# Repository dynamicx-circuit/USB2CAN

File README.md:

# USB2CAN
## 现在的问题
需要把USB2CAN移植成Kicad库版本

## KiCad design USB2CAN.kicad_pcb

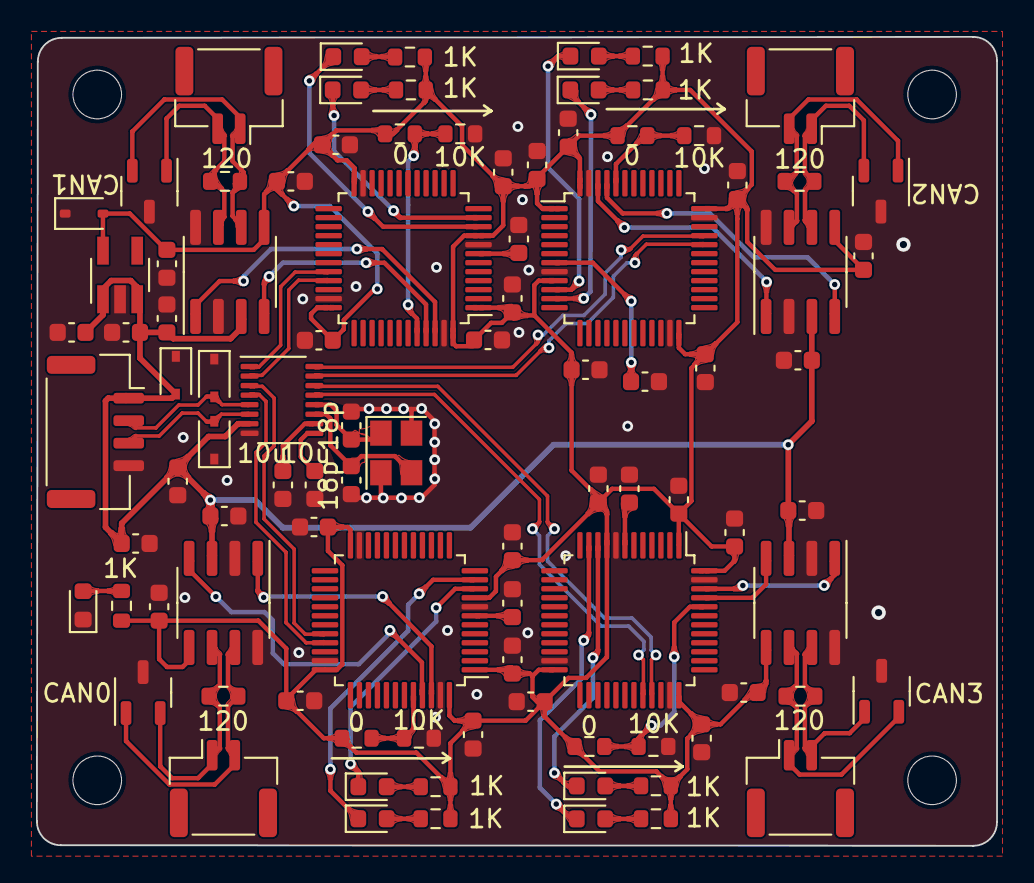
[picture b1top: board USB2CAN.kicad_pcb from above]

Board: 2 copper layers, 53.3 x 44.9 mm, 99 parts (0 on the bottom side), 58 nets.

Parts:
C1, C2, C3, C4, C5, C6, C7, C8, C9, C10, C11, C12, C13, C14, C15, C16, C17, C18, C19, C20, C21, C22, C23, C24, C25, C26, C27, C28, C29, C30, C31, C32, C33, C34, C35, C36, C41: 100n; C_0603_1608Metric
C37, C38: 10u; C_0603_1608Metric
C39, C40: 18p; C_0603_1608Metric
D1, D5, D6, D7, D8, D9, D10, D11, D12: LED; LED_0603_1608Metric
D2, D3, D4: BV05C; D_SOD-323
D13: BV03C; D_SOD-323
H1, H2, H3, H4: MountingHole; MountingHole_2.7mm_M2.5
J1: Conn_01x04; Molex_CLIK-Mate_502386-0470_1x04-1MP_P1.25mm_Horizontal
J2, J3, J4, J5: Conn_01x02; JST_GH_SM02B-GHS-TB_1x02-1MP_P1.25mm_Horizontal
R1, R4, R5, R9, R10, R14, R15, R19, R20: 1K; R_0603_1608Metric
R2, R7, R12, R17: 0; R_0603_1608Metric
R3, R8, R13, R18: 10K; R_0603_1608Metric
R6, R11, R16, R21: 120; R_0603_1608Metric
U1: HX9193; SOT-23-5_HandSoldering
U2, U4, U6, U8: STM32F072C8Tx; LQFP-48_7x7mm_P0.5mm
U3, U5, U7, U9: TJA1051T-3; SOIC-8_3.9x4.9mm_P1.27mm
U10: SL2.1S; SL2.1S-SSOP-16
U11, U12, U13, U14: SOT-23-3
Y1: 12M; Crystal_SMD_3225-4Pin_3.2x2.5mm

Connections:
+5V: C1.1, C2.1, C3.1, C12.1, C20.1, C28.1, C36.1, C41.1, D2.2 (A2), J1.1, U1.1 (VIN), U1.3 (EN), U3.3 (VCC), U5.3 (VCC), U7.3 (VCC), U9.3 (VCC), U10.7 (VDD5)
/STM1_CAN/CAN_H: J2.2, R11.1, U5.7 (CANH), U11.1 (H)
/STM1_CAN/CAN_L: J2.1, R11.2, U5.6 (CANL), U11.2 (L)
/STM1_CAN/CAN_RX: U4.45 (PB8), U5.4 (RXD)
/STM1_CAN/CAN_TX: U4.46 (PB9), U5.1 (TXD)
/STM1_CAN/LED1: D7.1 (K), U4.10 (PA0)
/STM1_CAN/LED2: D8.1 (K), U4.11 (PA1)
/STM1_CAN/USB_D+: U4.33 (PA12), U10.4 (DP1)
/STM1_CAN/USB_D-: U4.32 (PA11), U10.3 (DM1)
/STM2_CAN/CAN_H: J3.2, R6.1, U3.7 (CANH), U12.1 (H)
/STM2_CAN/CAN_L: J3.1, R6.2, U3.6 (CANL), U12.2 (L)
/STM2_CAN/CAN_RX: U2.45 (PB8), U3.4 (RXD)
/STM2_CAN/CAN_TX: U2.46 (PB9), U3.1 (TXD)
/STM2_CAN/LED1: D5.1 (K), U2.10 (PA0)
/STM2_CAN/LED2: D6.1 (K), U2.11 (PA1)
/STM2_CAN/USB_D+: U2.33 (PA12), U10.2 (DP2)
/STM2_CAN/USB_D-: U2.32 (PA11), U10.1 (DM2)
/STM_CAN3/CAN_H: J4.2, R21.1, U9.7 (CANH), U13.1 (H)
/STM_CAN3/CAN_L: J4.1, R21.2, U9.6 (CANL), U13.2 (L)
/STM_CAN3/CAN_RX: U8.45 (PB8), U9.4 (RXD)
/STM_CAN3/CAN_TX: U8.46 (PB9), U9.1 (TXD)
/STM_CAN3/LED1: D11.1 (K), U8.10 (PA0)
/STM_CAN3/LED2: D12.1 (K), U8.11 (PA1)
/STM_CAN3/USB_D+: U8.33 (PA12), U10.16 (DP3)
/STM_CAN3/USB_D-: U8.32 (PA11), U10.15 (DM3)
/STM_CAN4/CAN_H: J5.2, R16.1, U7.7 (CANH), U14.1 (H)
/STM_CAN4/CAN_L: J5.1, R16.2, U7.6 (CANL), U14.2 (L)
/STM_CAN4/CAN_RX: U6.45 (PB8), U7.4 (RXD)
/STM_CAN4/CAN_TX: U6.46 (PB9), U7.1 (TXD)
/STM_CAN4/LED1: D9.1 (K), U6.10 (PA0)
/STM_CAN4/LED2: D10.1 (K), U6.11 (PA1)
/STM_CAN4/USB_D+: U6.33 (PA12), U10.14 (DP4)
/STM_CAN4/USB_D-: U6.32 (PA11), U10.13 (DM4)
/USB_HUB/D+: D4.2 (A2), J1.3, U10.6 (UDP)
/USB_HUB/D-: D3.2 (A2), J1.2, U10.5 (UDM)
/USB_HUB/XIN: C40.1, U10.12 (XIN), Y1.1
/USB_HUB/XOUT: C39.1, U10.11 (XOUT), Y1.3
GND: C1.2, C2.2, C3.2, C4.2, C5.1, C6.2, C7.2, C8.2, C9.2, C10.2, C11.2, C12.2, C13.1, C14.2, C15.2, C16.2, C17.2, C18.2, C19.2, C20.2, C21.1, C22.2, C23.2, C24.2, C25.2, C26.2, C27.2, C28.2, C29.1, C30.2, C31.2, C32.2, C33.2, C34.2, C35.2, C36.2, C37.2, C38.2, C39.2, C40.2, C41.2, D1.1 (K), D2.1 (A1), D3.1 (A1), D4.1 (A1), D13.1 (A1), J1.4, R3.1, R8.1, R13.1, R18.1, U1.2 (GND), U2.8 (VSSA), U2.23 (VSS), U2.35 (VSS), U2.47 (VSS), U3.2 (GND), U3.8 (S), U4.8 (VSSA), U4.23 (VSS), U4.35 (VSS), U4.47 (VSS), U5.2 (GND), U5.8 (S), U6.8 (VSSA), U6.23 (VSS), U6.35 (VSS), U6.47 (VSS), U7.2 (GND), U7.8 (S), U8.8 (VSSA), U8.23 (VSS), U8.35 (VSS), U8.47 (VSS), U9.2 (GND), U9.8 (S), U10.8 (VSS), U11.3 (GND), U12.3 (GND), U13.3 (GND), U14.3 (GND), Y1.2, Y1.4
unnamed: D1.2 (A), R1.2
unnamed: D5.2 (A), R4.1
unnamed: D6.2 (A), R5.1
unnamed: D7.2 (A), R9.1
unnamed: D8.2 (A), R10.1
unnamed: D9.2 (A), R14.1
unnamed: D10.2 (A), R15.1
unnamed: D11.2 (A), R19.1
unnamed: D12.2 (A), R20.1
unnamed: R2.1, R3.2, U2.44 (BOOT0)
unnamed: C5.2, U2.7 (NRST)
unnamed: R7.1, R8.2, U4.44 (BOOT0)
unnamed: C13.2, U4.7 (NRST)
unnamed: R12.1, R13.2, U6.44 (BOOT0)
unnamed: C21.2, U6.7 (NRST)
unnamed: R17.1, R18.2, U8.44 (BOOT0)
unnamed: C29.2, U8.7 (NRST)
unnamed: C38.1, U10.10 (VDD18)
unnamed: C37.1, U10.9 (VDD33)
VCC: C4.1, C6.1, C7.1, C8.1, C9.1, C10.1, C11.1, C14.1, C15.1, C16.1, C17.1, C18.1, C19.1, C22.1, C23.1, C24.1, C25.1, C26.1, C27.1, C30.1, C31.1, C32.1, C33.1, C34.1, C35.1, D13.2 (A2), R1.1, R2.2, R4.2, R5.2, R7.2, R9.2, R10.2, R12.2, R14.2, R15.2, R17.2, R19.2, R20.2, U1.5 (VOUT), U2.1 (VBAT), U2.9 (VDDA), U2.24 (VDD), U2.36 (VDDIO2), U2.48 (VDD), U3.5 (VIO), U4.1 (VBAT), U4.9 (VDDA), U4.24 (VDD), U4.36 (VDDIO2), U4.48 (VDD), U5.5 (VIO), U6.1 (VBAT), U6.9 (VDDA), U6.24 (VDD), U6.36 (VDDIO2), U6.48 (VDD), U7.5 (VIO), U8.1 (VBAT), U8.9 (VDDA), U8.24 (VDD), U8.36 (VDDIO2), U8.48 (VDD), U9.5 (VIO)

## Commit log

2022-07-01 Add .gitignore and README.md
2022-07-01 Add USB2CAN original version
2022-07-04 test
2023-04-28 Add ESD protection
